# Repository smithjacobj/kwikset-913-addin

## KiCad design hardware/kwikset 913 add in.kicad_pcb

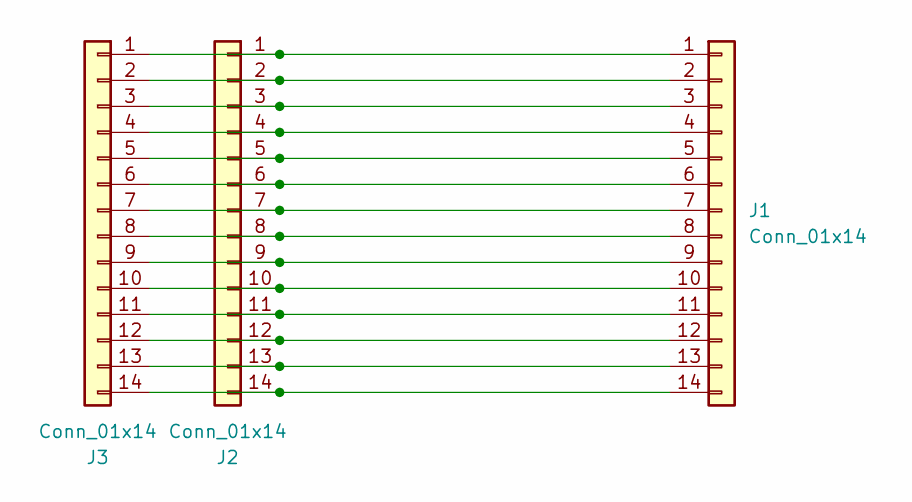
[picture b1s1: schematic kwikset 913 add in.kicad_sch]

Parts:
J1: Conn_01x14; PinHeader_1x14_P2.00mm_Horizontal
J2: Conn_01x14; PinHeader_1x14_P2.54mm_Vertical
J3: Conn_01x14; PinSocket_1x14_P2.00mm_Horizontal

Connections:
unnamed: J1.1, J2.1, J3.1
unnamed: J1.2, J2.2, J3.2
unnamed: J1.3, J2.3, J3.3
unnamed: J1.4, J2.4, J3.4
unnamed: J1.5, J2.5, J3.5
unnamed: J1.6, J2.6, J3.6
unnamed: J1.7, J2.7, J3.7
unnamed: J1.8, J2.8, J3.8
unnamed: J1.9, J2.9, J3.9
unnamed: J1.10, J2.10, J3.10
unnamed: J1.11, J2.11, J3.11
unnamed: J1.12, J2.12, J3.12
unnamed: J1.13, J2.13, J3.13
unnamed: J1.14, J2.14, J3.14

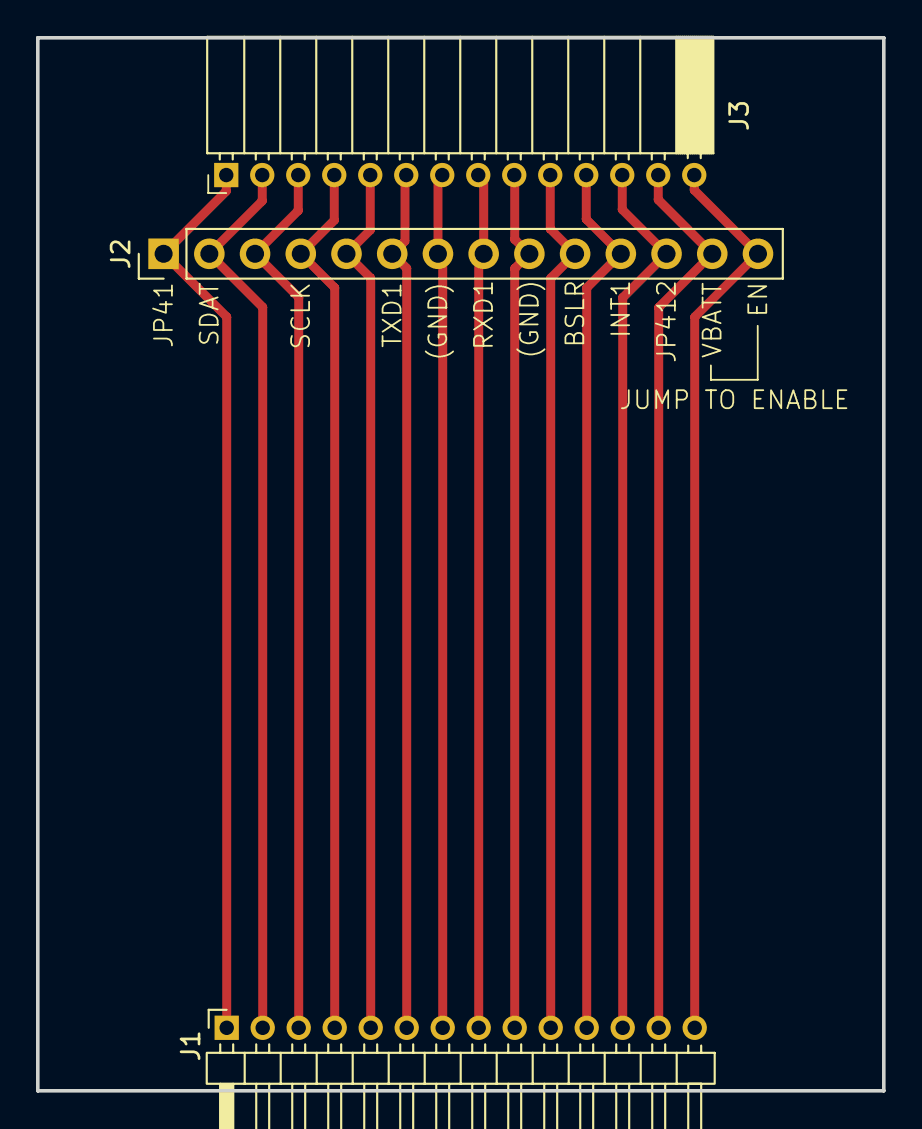
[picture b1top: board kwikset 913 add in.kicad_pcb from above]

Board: 2 copper layers, 47.0 x 58.5 mm, 3 parts (0 on the bottom side), 14 nets.
